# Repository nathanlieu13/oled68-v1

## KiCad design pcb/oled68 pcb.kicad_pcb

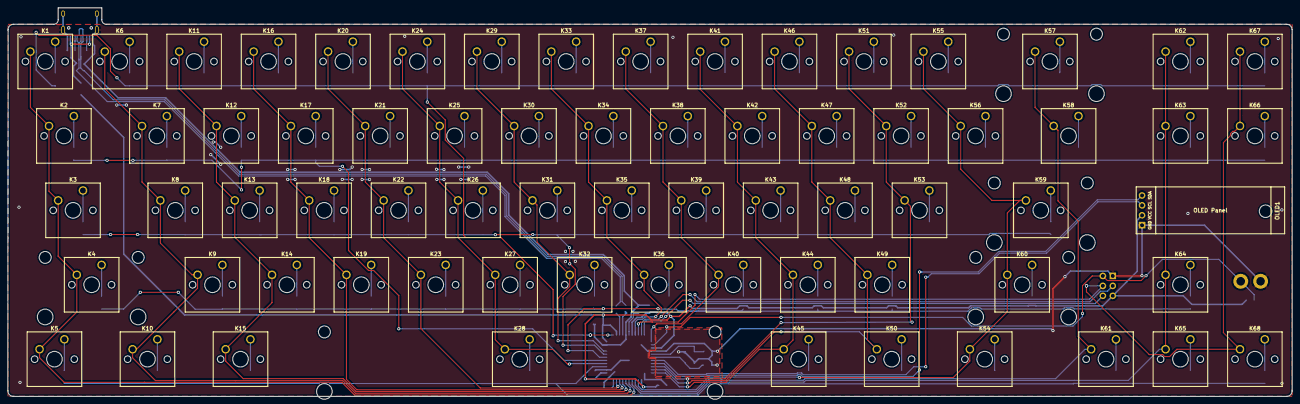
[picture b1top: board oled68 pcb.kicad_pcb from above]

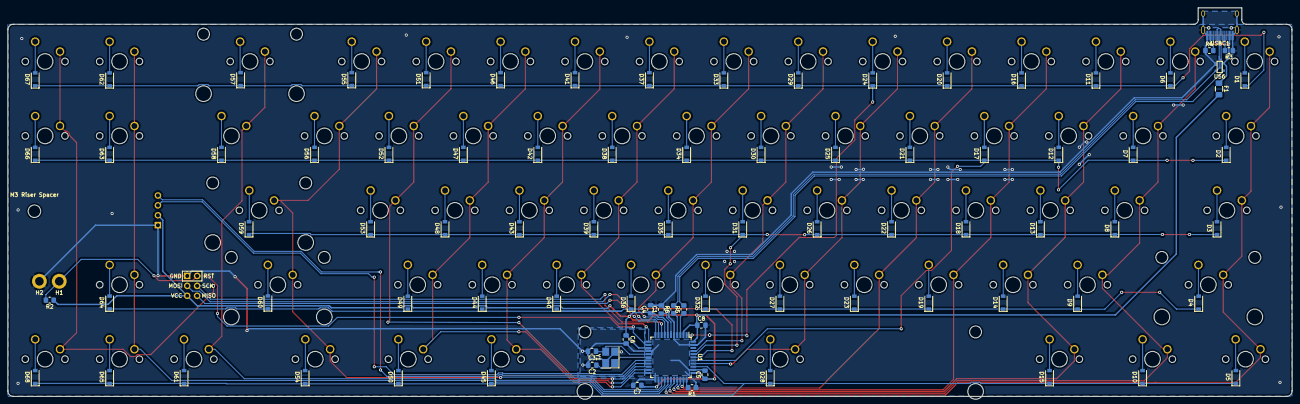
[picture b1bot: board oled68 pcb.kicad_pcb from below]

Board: 2 copper layers, 328.7 x 99.4 mm, 160 parts (91 on the bottom side), 105 nets.

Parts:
C1: 1u; C_0805_2012Metric_Pad1.18x1.45mm_HandSolder
C2, C3: 22pf cap; C_0805_2012Metric_Pad1.18x1.45mm_HandSolder
C4, C5, C6, C7: 0.1u; C_0805_2012Metric_Pad1.18x1.45mm_HandSolder
C8: 10u; C_0805_2012Metric_Pad1.18x1.45mm_HandSolder
D1, D2, D3, D4, D5, D6, D7, D8, D9, D10, D11, D12, D13, D14, D15, D16, D17, D18, D19, D20, D21, D22, D23, D24, D25, D26, D27, D28, D29, D30, D31, D32, D33, D34, D35, D36, D37, D38, D39, D40, D41, D42, D43, D44, D45, D46, D47, D48, D49, D50, D51, D52, D53, D54, D55, D56, D57, D58, D59, D60, D61, D62, D63, D64, D65, D66, D67, D68: D; D_SOD-123
F1: 500m polyfuse; Fuse_1206_3216Metric_Pad1.42x1.75mm_HandSolder
H1, H2: JUMP TO RESET; MountingHole_2.2mm_M2_DIN965_Pad
J1: AVR-ISP-6; Reset_Pretty-Mask
K1: ESC; SW_Cherry_MX_1.00u_PCB
K2: TAB; SW_Cherry_MX_1.50u_PCB
K3: CAPS; SW_Cherry_MX_1.75u_PCB
K4: LSHIFT; SW_Cherry_MX_2.25u_PCB
K5: LCTRL; SW_Cherry_MX_1.25u_PCB
K6: 1; SW_Cherry_MX_1.00u_PCB
K7: Q; SW_Cherry_MX_1.00u_PCB
K8: A; SW_Cherry_MX_1.00u_PCB
K9: Z; SW_Cherry_MX_1.00u_PCB
K10: WIN; SW_Cherry_MX_1.25u_PCB
K11: 2; SW_Cherry_MX_1.00u_PCB
K12: W; SW_Cherry_MX_1.00u_PCB
K13: S; SW_Cherry_MX_1.00u_PCB
K14: X; SW_Cherry_MX_1.00u_PCB
K15: LALT; SW_Cherry_MX_1.25u_PCB
K16: 3; SW_Cherry_MX_1.00u_PCB
K17: E; SW_Cherry_MX_1.00u_PCB
K18: D; SW_Cherry_MX_1.00u_PCB
K19: C; SW_Cherry_MX_1.00u_PCB
K20: 4; SW_Cherry_MX_1.00u_PCB
K21: R; SW_Cherry_MX_1.00u_PCB
K22: F; SW_Cherry_MX_1.00u_PCB
K23: V; SW_Cherry_MX_1.00u_PCB
K24: 5; SW_Cherry_MX_1.00u_PCB
K25: T; SW_Cherry_MX_1.00u_PCB
K26: G; SW_Cherry_MX_1.00u_PCB
K27: B; SW_Cherry_MX_1.00u_PCB
K28: SPACE; SW_Cherry_MX_6.25u_PCB
K29: 6; SW_Cherry_MX_1.00u_PCB
K30: Y; SW_Cherry_MX_1.00u_PCB
K31: H; SW_Cherry_MX_1.00u_PCB
K32: N; SW_Cherry_MX_1.00u_PCB
K33: 7; SW_Cherry_MX_1.00u_PCB
K34: U; SW_Cherry_MX_1.00u_PCB
K35: J; SW_Cherry_MX_1.00u_PCB
K36: M; SW_Cherry_MX_1.00u_PCB
K37: 8; SW_Cherry_MX_1.00u_PCB
K38: I; SW_Cherry_MX_1.00u_PCB
K39: K; SW_Cherry_MX_1.00u_PCB
K40: ,; SW_Cherry_MX_1.00u_PCB
K41: 9; SW_Cherry_MX_1.00u_PCB
K42: O; SW_Cherry_MX_1.00u_PCB
K43: L; SW_Cherry_MX_1.00u_PCB
K44: .; SW_Cherry_MX_1.00u_PCB
K45: RALT; SW_Cherry_MX_1.25u_PCB
K46: 0; SW_Cherry_MX_1.00u_PCB
K47: P; SW_Cherry_MX_1.00u_PCB
K48: ;; SW_Cherry_MX_1.00u_PCB
K49: /; SW_Cherry_MX_1.00u_PCB
K50: FN; SW_Cherry_MX_1.25u_PCB
K51: -; SW_Cherry_MX_1.00u_PCB
K52: [; SW_Cherry_MX_1.00u_PCB
K53: '; SW_Cherry_MX_1.00u_PCB
K54: RCTRL; SW_Cherry_MX_1.25u_PCB
K55: =; SW_Cherry_MX_1.00u_PCB
K56: ]; SW_Cherry_MX_1.00u_PCB
K57: BACK; SW_Cherry_MX_2.00u_PCB
K58: \; SW_Cherry_MX_1.50u_Plate
K59: ENTER; SW_Cherry_MX_2.25u_PCB
K60: RSHIFT; SW_Cherry_MX_2.75u_PCB
K61: LEFT; SW_Cherry_MX_1.00u_PCB
K62: PGUP; SW_Cherry_MX_1.00u_PCB
K63: PGDN; SW_Cherry_MX_1.00u_PCB
K64: UP; SW_Cherry_MX_1.00u_PCB
K65: DOWN; SW_Cherry_MX_1.00u_PCB
K66: INS; SW_Cherry_MX_1.00u_PCB
K67: DEL; SW_Cherry_MX_1.00u_PCB
K68: RIGHT; SW_Cherry_MX_1.00u_PCB
M3 Riser Spacer: M3 Riser Spacer; MountingHole_3.2mm_M3
OLED1: SSD13064pin; SSD1306-0.91-OLED-4pin-128x32
R1, R2: 10k; R_0805_2012Metric_Pad1.20x1.40mm_HandSolder
R3, R4: 5.1k res; R_0805_2012Metric_Pad1.20x1.40mm_HandSolder
R5: 22ohm resistor; R_0805_2012Metric_Pad1.20x1.40mm_HandSolder
R6: 22ohm resisitor; R_0805_2012Metric_Pad1.20x1.40mm_HandSolder
U1: ATmega32U4-AU; TQFP-44_10x10mm_P0.8mm
U56: PRTR5V0U2X; SOT143B
USBC1: HRO-TYPE-C-31-M-12; HRO-TYPE-C-31-M-12-HandSoldering
Y1: XTAL; Crystal_SMD_3225-4Pin_3.2x2.5mm_HandSoldering

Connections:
+5V: C4.1, C5.1, C6.1, C7.1, C8.1, F1.2, J1.2, OLED1.2, R2.1, U1.2, U1.7, U1.14, U1.24, U1.34, U1.44
D+: R6.1, R6.2, U1.4, U56.2, USBC1.6, USBC1.8
D-: R5.1, R5.2, U1.3, U56.3, USBC1.5, USBC1.7
GND: C1.2, C2.2, C3.2, C4.2, C5.2, C6.2, C7.2, C8.2, H2.1, J1.6, OLED1.1, R1.1, R3.1, R4.1, U1.5, U1.15, U1.23, U1.35, U1.43, U56.1, USBC1.1, USBC1.12, USBC1.13, Y1.2, Y1.4
MISO: J1.1, U1.11
MOSI: J1.4, U1.10
unnamed: C1.1, U1.6
unnamed: D1.2, K1.1
unnamed: D2.2, K2.1
unnamed: D3.2, K3.1
unnamed: D4.2, K4.1
unnamed: D5.2, K5.1
unnamed: D6.2, K6.1
unnamed: D7.2, K7.1
unnamed: D8.2, K8.1
unnamed: D9.2, K9.1
unnamed: D10.2, K10.1
unnamed: D11.2, K11.1
unnamed: D12.2, K12.1
unnamed: D13.2, K13.1
unnamed: D14.2, K14.1
unnamed: D15.2, K15.1
unnamed: D16.2, K16.1
unnamed: D17.2, K17.1
unnamed: D18.2, K18.1
unnamed: D19.2, K19.1
unnamed: D20.2, K20.1
unnamed: D21.2, K21.1
unnamed: D22.2, K22.1
unnamed: D23.2, K23.1
unnamed: D24.2, K24.1
unnamed: D25.2, K25.1
unnamed: D26.2, K26.1
unnamed: D27.2, K27.1
unnamed: D28.2, K28.1
unnamed: D29.2, K29.1
unnamed: D30.2, K30.1
unnamed: D31.2, K31.1
unnamed: D32.2, K32.1
unnamed: D33.2, K33.1
unnamed: D34.2, K34.1
unnamed: D35.2, K35.1
unnamed: D36.2, K36.1
unnamed: D37.2, K37.1
unnamed: D38.2, K38.1
unnamed: D39.2, K39.1
unnamed: D40.2, K40.1
unnamed: D41.2, K41.1
unnamed: D42.2, K42.1
unnamed: D43.2, K43.1
unnamed: D44.2, K44.1
unnamed: D45.2, K45.1
unnamed: D46.2, K46.1
unnamed: D47.2, K47.1
unnamed: D48.2, K48.1
unnamed: D49.2, K49.1
unnamed: D50.2, K50.1
unnamed: D51.2, K51.1
unnamed: D52.2, K52.1
unnamed: D53.2, K53.1
unnamed: D54.2, K54.1
unnamed: D55.2, K55.1
unnamed: D56.2, K56.1
unnamed: D57.2, K57.1
unnamed: D58.2, K58.1
unnamed: D59.2, K59.1
unnamed: D60.2, K60.1
unnamed: D61.2, K61.1
unnamed: D62.2, K62.1
unnamed: D63.2, K63.1
unnamed: D64.2, K64.1
unnamed: D65.2, K65.1
unnamed: D66.2, K66.1
unnamed: D67.2, K67.1
unnamed: D68.2, K68.1
unnamed: OLED1.3, U1.18
unnamed: OLED1.4, U1.19
unnamed: R1.2, U1.33
unnamed: R4.2, USBC1.10
unnamed: R3.2, USBC1.4
RESET: H1.1, J1.5, R2.2, U1.13
SCK_col15: J1.3, K66.2, K67.2, K68.2, U1.9
VCC: F1.1, U56.4, USBC1.2, USBC1.11
XTAL1: C2.1, U1.17, Y1.1
XTAL2: C3.1, U1.16, Y1.3
col0: K1.2, K2.2, K3.2, K4.2, K5.2, U1.28
col1: K6.2, K7.2, K8.2, K9.2, K10.2, U1.29
col2: K11.2, K12.2, K13.2, K14.2, K15.2, U1.30
col3: K16.2, K17.2, K18.2, K19.2, U1.31
col4: K20.2, K21.2, K22.2, K23.2, U1.32
col5: K24.2, K25.2, K26.2, K27.2, K28.2, U1.37
col6: K29.2, K30.2, K31.2, K32.2, U1.41
col7: K33.2, K34.2, K35.2, K36.2, U1.8
col8: K37.2, K38.2, K39.2, K40.2, U1.12
col9: K41.2, K42.2, K43.2, K44.2, K45.2, U1.22
col10: K46.2, K47.2, K48.2, K49.2, K50.2, U1.21
col11: K51.2, K52.2, K53.2, U1.20
col12: K54.2, K55.2, K56.2, K59.2, K60.2, U1.25
col13: K57.2, K58.2, K61.2, U1.26
col14: K62.2, K63.2, K64.2, K65.2, U1.27
row0: D1.1, D6.1, D11.1, D16.1, D20.1, D24.1, D29.1, D33.1, D37.1, D41.1, D46.1, D51.1, D55.1, D57.1, D62.1, D67.1, U1.1
row1: D2.1, D7.1, D12.1, D17.1, D21.1, D25.1, D30.1, D34.1, D38.1, D42.1, D47.1, D52.1, D56.1, D58.1, D63.1, D66.1, U1.38
row2: D3.1, D8.1, D13.1, D18.1, D22.1, D26.1, D31.1, D35.1, D39.1, D43.1, D48.1, D53.1, D59.1, U1.40
row3: D4.1, D9.1, D14.1, D19.1, D23.1, D27.1, D32.1, D36.1, D40.1, D44.1, D49.1, D60.1, D64.1, U1.39
row4: D5.1, D10.1, D15.1, D28.1, D45.1, D50.1, D54.1, D61.1, D65.1, D68.1, U1.36
